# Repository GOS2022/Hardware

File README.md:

# Hardware
This repository contains the design and production files of hardware projects.

# Description
The main goal of hardware projects is to create a compact test device for the OS and service tests.

# Remarks
Contribution to this project is encouraged and appriciated.
If you have any questions or ideas, feel free to contact me: ahmedibrahim.gazar97@gmail.com

Last updated: 2025-07-04
(c) 2025, Ahmed Gazar

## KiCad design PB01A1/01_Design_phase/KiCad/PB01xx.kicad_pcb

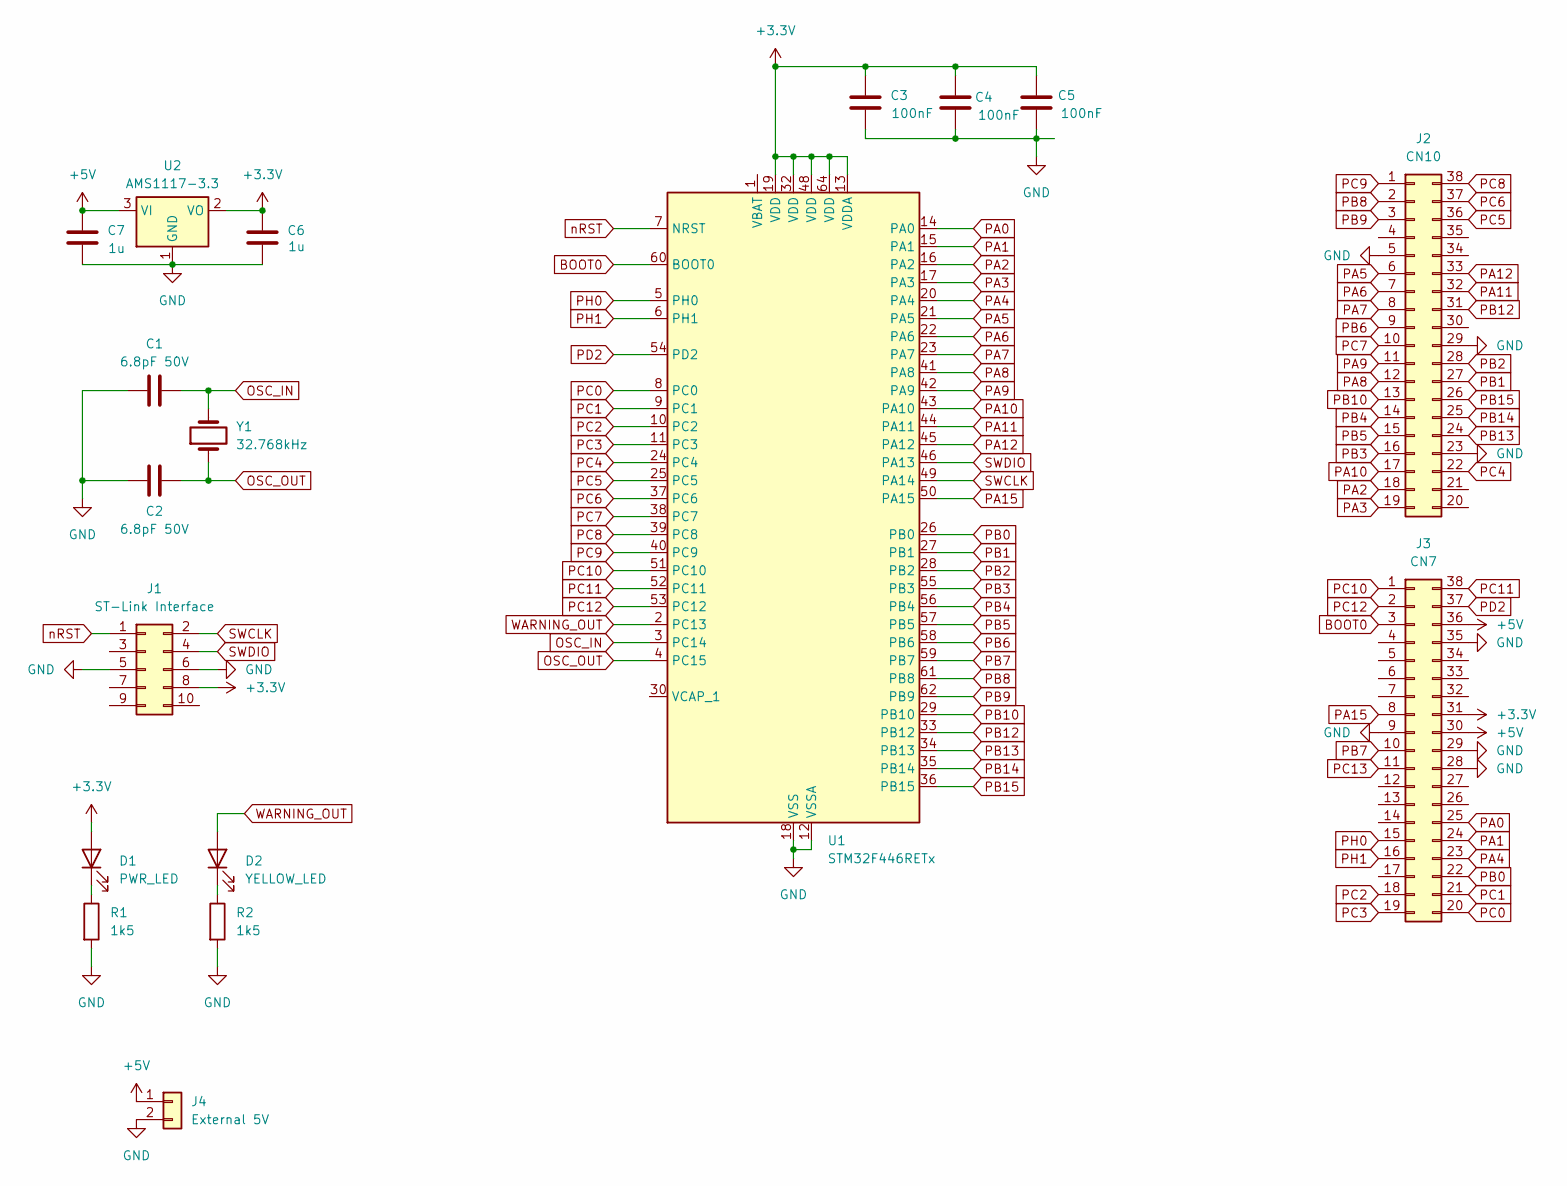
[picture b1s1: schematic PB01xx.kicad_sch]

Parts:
C1, C2: 6.8pF 50V; C_1206_3216Metric_Pad1.33x1.80mm_HandSolder
C3, C4, C5: 100nF; C_1206_3216Metric_Pad1.33x1.80mm_HandSolder
C6, C7: 1u; C_1206_3216Metric_Pad1.33x1.80mm_HandSolder
D1: PWR_LED; LED_1206_3216Metric_Pad1.42x1.75mm_HandSolder
D2: YELLOW_LED; LED_1206_3216Metric_Pad1.42x1.75mm_HandSolder
J1: ST-Link Interface; IDC-Header_2x05_P2.54mm_Vertical
J2: CN10; PinHeader_2x19_P2.54mm_Vertical
J3: CN7; PinHeader_2x19_P2.54mm_Vertical
J4: External 5V; PinHeader_1x02_P2.54mm_Vertical
R1, R2: 1k5; R_1206_3216Metric_Pad1.30x1.75mm_HandSolder
U1: STM32F446RETx; LQFP-64_10x10mm_P0.5mm
U2: AMS1117-3.3; SOT-223-3_TabPin2
Y1: 32.768kHz; Crystal_Round_D3.0mm_Vertical

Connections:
+3.3V: C3.1, C4.1, C5.1, C6.1, D1.2 (A), J1.8, J3.31, U1.13 (VDDA), U1.19 (VDD), U1.32 (VDD), U1.48 (VDD), U1.64 (VDD), U2.2 (VO)
+5V: C7.1, J3.30, J3.36, J4.1, U2.3 (VI)
BOOT0: J3.3, U1.60 (BOOT0)
GND: C1.1, C2.1, C3.2, C4.2, C5.2, C6.2, C7.2, J1.5, J1.6, J2.5, J2.23, J2.29, J3.9, J3.28, J3.29, J3.35, J4.2, R1.2, R2.2, U1.12 (VSSA), U1.18 (VSS), U1.31 (VSS), U1.47 (VSS), U1.63 (VSS), U2.1 (GND)
unnamed: D1.1 (K), R1.1
unnamed: D2.1 (K), R2.1
OSC_IN: C1.2, U1.3 (PC14), Y1.2
OSC_OUT: C2.2, U1.4 (PC15), Y1.1
PA0: J3.25, U1.14 (PA0)
PA1: J3.24, U1.15 (PA1)
PA2: J2.18, U1.16 (PA2)
PA3: J2.19, U1.17 (PA3)
PA4: J3.23, U1.20 (PA4)
PA5: J2.6, U1.21 (PA5)
PA6: J2.7, U1.22 (PA6)
PA7: J2.8, U1.23 (PA7)
PA8: J2.12, U1.41 (PA8)
PA9: J2.11, U1.42 (PA9)
PA10: J2.17, U1.43 (PA10)
PA11: J2.32, U1.44 (PA11)
PA12: J2.33, U1.45 (PA12)
PA15: J3.8, U1.50 (PA15)
PB0: J3.22, U1.26 (PB0)
PB1: J2.27, U1.27 (PB1)
PB2: J2.28, U1.28 (PB2)
PB3: J2.16, U1.55 (PB3)
PB4: J2.14, U1.56 (PB4)
PB5: J2.15, U1.57 (PB5)
PB6: J2.9, U1.58 (PB6)
PB7: J3.10, U1.59 (PB7)
PB8: J2.2, U1.61 (PB8)
PB9: J2.3, U1.62 (PB9)
PB10: J2.13, U1.29 (PB10)
PB12: J2.31, U1.33 (PB12)
PB13: J2.24, U1.34 (PB13)
PB14: J2.25, U1.35 (PB14)
PB15: J2.26, U1.36 (PB15)
PC0: J3.20, U1.8 (PC0)
PC1: J3.21, U1.9 (PC1)
PC2: J3.18, U1.10 (PC2)
PC3: J3.19, U1.11 (PC3)
PC4: J2.22, U1.24 (PC4)
PC5: J2.36, U1.25 (PC5)
PC6: J2.37, U1.37 (PC6)
PC7: J2.10, U1.38 (PC7)
PC8: J2.38, U1.39 (PC8)
PC9: J2.1, U1.40 (PC9)
PC10: J3.1, U1.51 (PC10)
PC11: J3.38, U1.52 (PC11)
PC12: J3.2, U1.53 (PC12)
PC13: J3.11
PD2: J3.37, U1.54 (PD2)
PH0: J3.15, U1.5 (PH0)
PH1: J3.16, U1.6 (PH1)
SWCLK: J1.2, U1.49 (PA14)
SWDIO: J1.4, U1.46 (PA13)
WARNING_OUT: D2.2 (A), U1.2 (PC13)
nRST: J1.1, U1.7 (NRST)

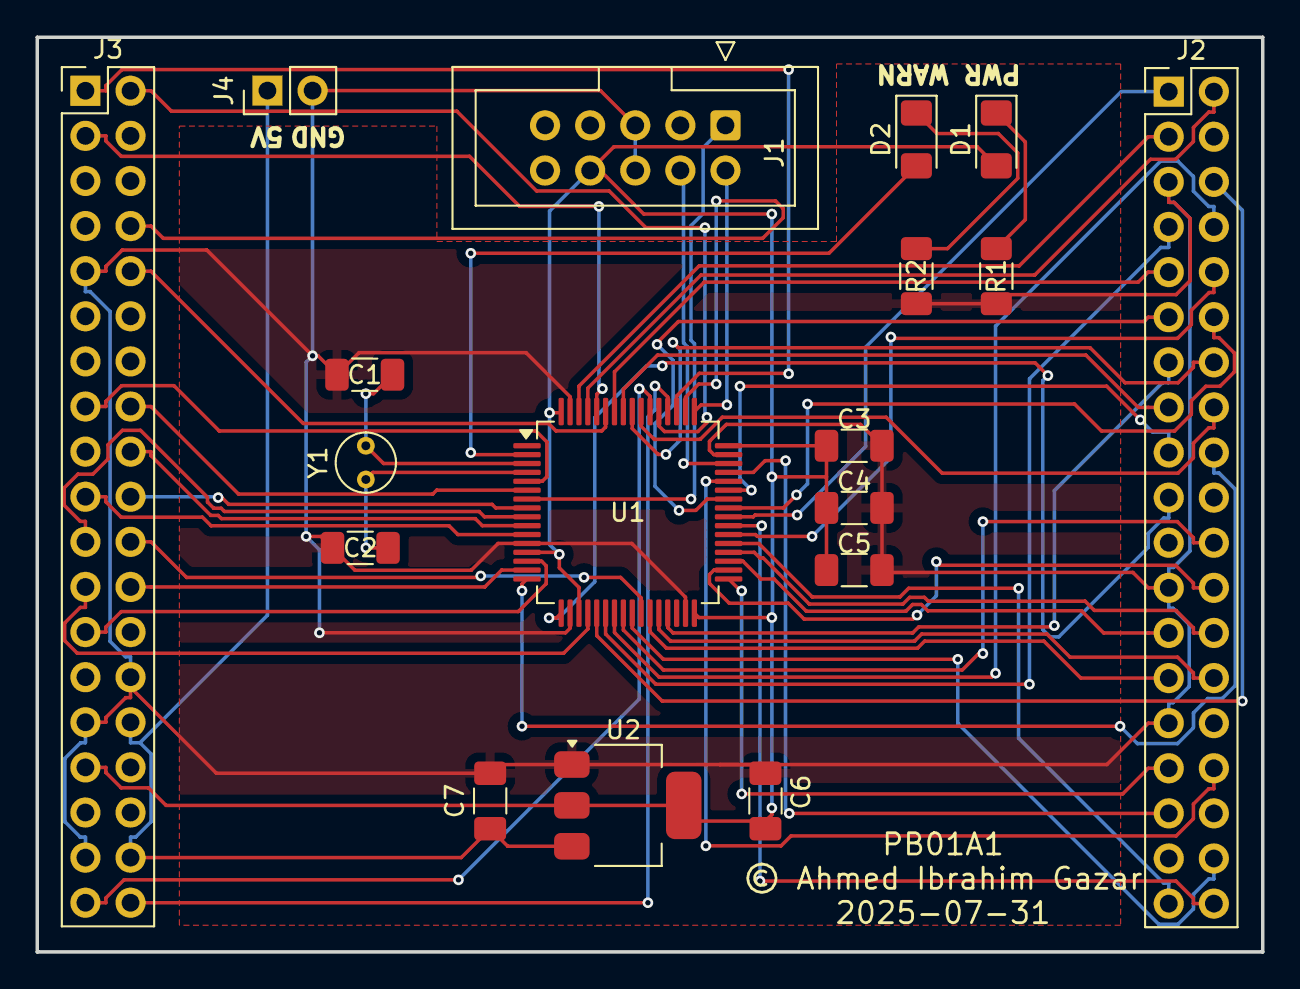
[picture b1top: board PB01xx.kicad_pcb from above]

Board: 2 copper layers, 69.0 x 51.5 mm, 18 parts (0 on the bottom side), 57 nets.

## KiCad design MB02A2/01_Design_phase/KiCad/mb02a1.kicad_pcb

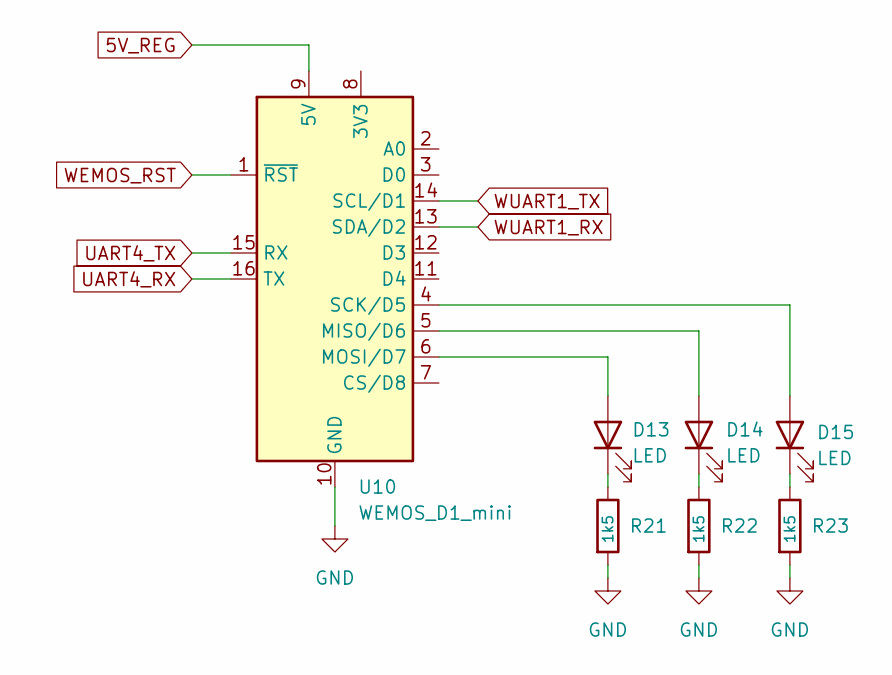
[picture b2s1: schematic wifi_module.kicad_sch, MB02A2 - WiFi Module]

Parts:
D13, D14, D15: LED; LED_1206_3216Metric
R21, R22, R23: 1k5; R_0805_2012Metric
U10: WEMOS_D1_mini; WEMOS_D1_mini_light

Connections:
5V_REG: U10.9 (5V); also elsewhere on the board
GND: R21.2, R22.2, R23.2, U10.10 (GND); also elsewhere on the board
unnamed: D13.2 (A), U10.6 (MOSI/D7)
unnamed: D13.1 (K), R21.1
unnamed: D14.2 (A), U10.5 (MISO/D6)
unnamed: D14.1 (K), R22.1
unnamed: D15.2 (A), U10.4 (SCK/D5)
unnamed: D15.1 (K), R23.1
UART4_RX: U10.16 (TX); also elsewhere on the board
UART4_TX: U10.15 (RX); also elsewhere on the board
WEMOS_RST: U10.1 (~RST); also elsewhere on the board
WUART1_RX: U10.13 (SDA/D2); also elsewhere on the board
WUART1_TX: U10.14 (SCL/D1); also elsewhere on the board

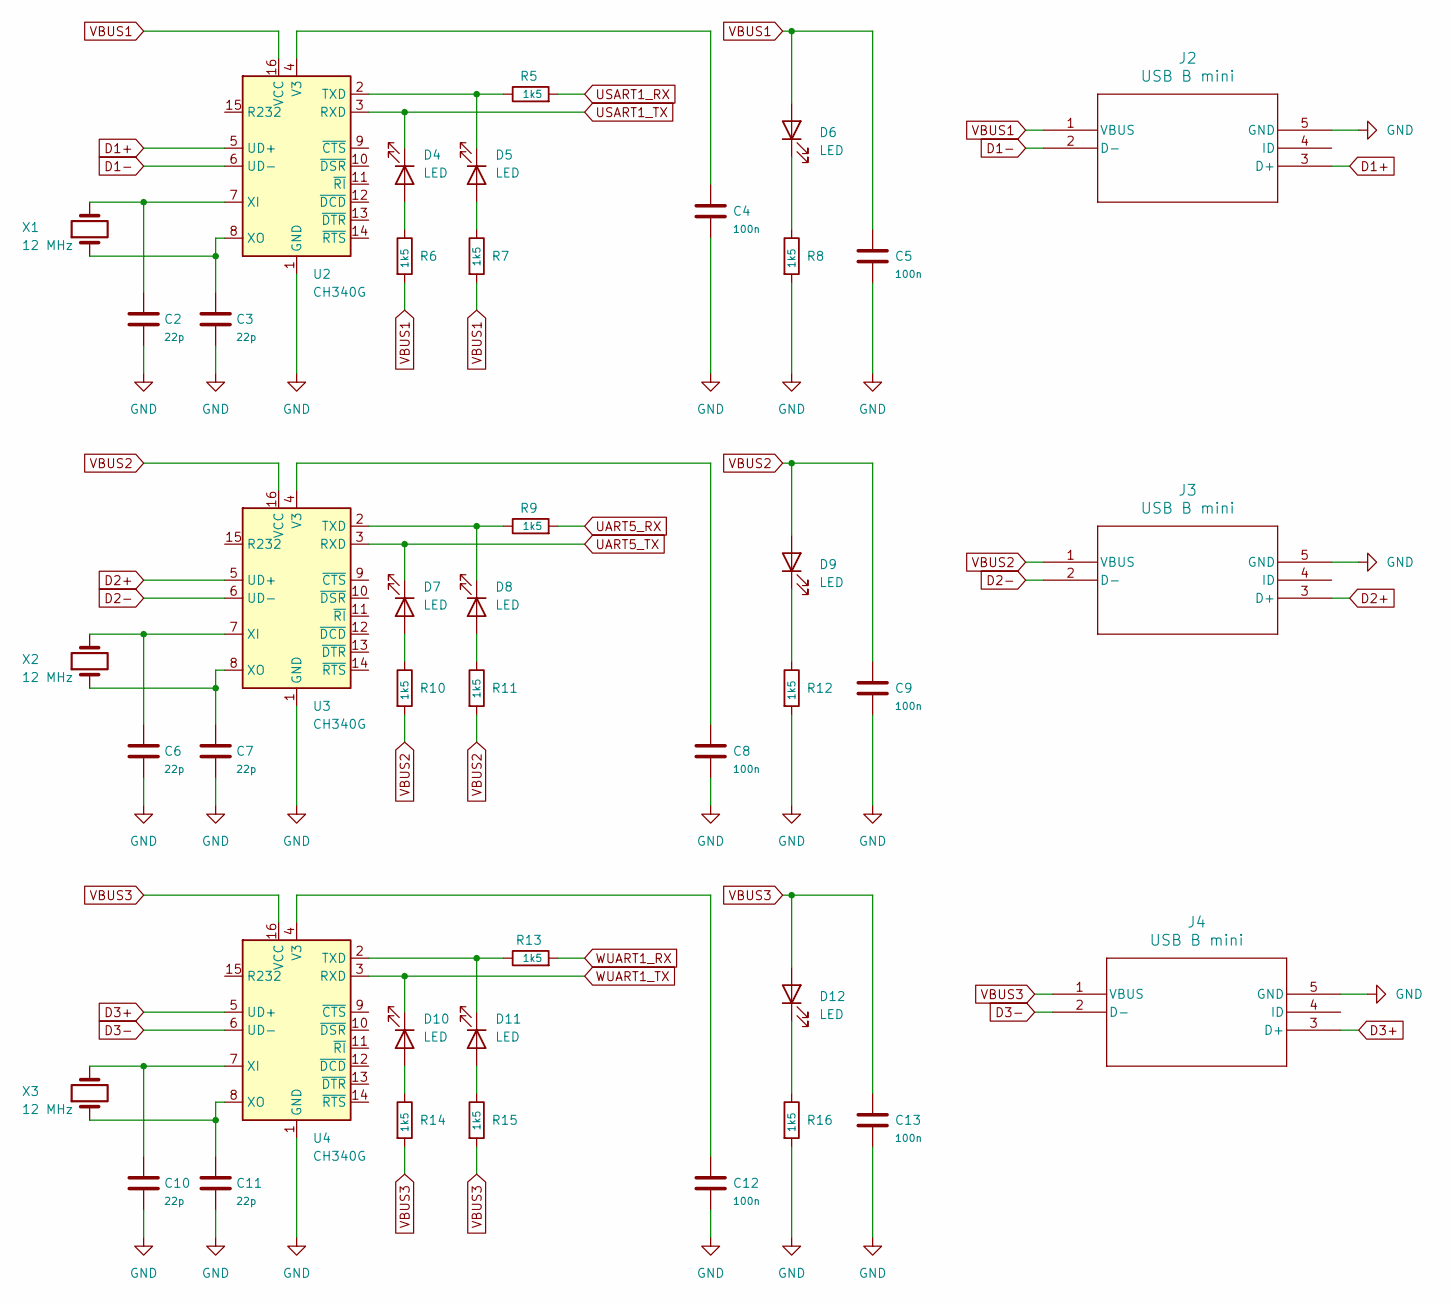
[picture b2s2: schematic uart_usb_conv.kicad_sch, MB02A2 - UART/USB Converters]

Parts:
C2, C3, C6, C7, C10, C11: 22p; C_0805_2012Metric
C4, C5, C8, C9, C12, C13: 100n; C_0805_2012Metric
D4, D5, D6, D7, D8, D9, D10, D11, D12: LED; LED_1206_3216Metric
J2, J3, J4: USB B mini; 54819-0519_MOL
R5, R6, R7, R8, R9, R10, R11, R12, R13, R14, R15, R16: 1k5; R_0805_2012Metric
U2, U3, U4: CH340G; SOIC-16_3.9x9.9mm_P1.27mm
X1, X2, X3: 12 MHz; Crystal_HC49-U_Vertical

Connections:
D1+: J2.3 (D+), U2.5 (UD+)
D1-: J2.2 (D-), U2.6 (UD-)
D2+: J3.3 (D+), U3.5 (UD+)
D2-: J3.2 (D-), U3.6 (UD-)
D3+: J4.3 (D+), U4.5 (UD+)
D3-: J4.2 (D-), U4.6 (UD-)
GND: C2.2, C3.2, C4.2, C5.2, C6.2, C7.2, C8.2, C9.2, C10.2, C11.2, C12.2, C13.2, J2.5 (GND), J3.5 (GND), J4.5 (GND), R8.2, R12.2, R16.2, U2.1 (GND), U3.1 (GND), U4.1 (GND); also elsewhere on the board
unnamed: D4.2 (A), R6.1
unnamed: D5.2 (A), R7.1
unnamed: D5.1 (K), R5.1, U2.2 (TXD)
unnamed: D6.1 (K), R8.1
unnamed: D7.2 (A), R10.1
unnamed: D8.2 (A), R11.1
unnamed: D8.1 (K), R9.1, U3.2 (TXD)
unnamed: D9.1 (K), R12.1
unnamed: D10.2 (A), R14.1
unnamed: D11.2 (A), R15.1
unnamed: D11.1 (K), R13.1, U4.2 (TXD)
unnamed: D12.1 (K), R16.1
unnamed: C4.1, U2.4 (V3)
unnamed: C2.1, U2.7 (XI), X1.2
unnamed: C3.1, U2.8 (XO), X1.1
unnamed: C8.1, U3.4 (V3)
unnamed: C6.1, U3.7 (XI), X2.2
unnamed: C7.1, U3.8 (XO), X2.1
unnamed: C12.1, U4.4 (V3)
unnamed: C10.1, U4.7 (XI), X3.2
unnamed: C11.1, U4.8 (XO), X3.1
UART5_RX: R9.2; also elsewhere on the board
UART5_TX: D7.1 (K), U3.3 (RXD); also elsewhere on the board
USART1_RX: R5.2; also elsewhere on the board
USART1_TX: D4.1 (K), U2.3 (RXD); also elsewhere on the board
VBUS1: C5.1, D6.2 (A), J2.1 (VBUS), R6.2, R7.2, U2.16 (VCC)
VBUS2: C9.1, D9.2 (A), J3.1 (VBUS), R10.2, R11.2, U3.16 (VCC)
VBUS3: C13.1, D12.2 (A), J4.1 (VBUS), R14.2, R15.2, U4.16 (VCC)
WUART1_RX: R13.2; also elsewhere on the board
WUART1_TX: D10.1 (K), U4.3 (RXD); also elsewhere on the board

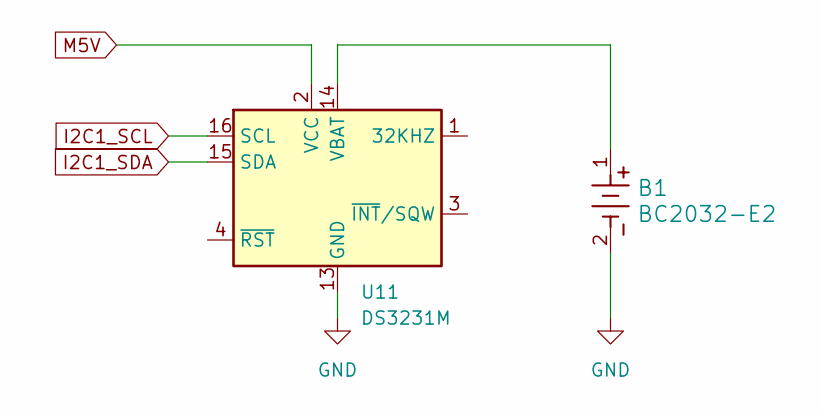
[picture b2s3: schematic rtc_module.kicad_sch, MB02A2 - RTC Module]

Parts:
B1: BC2032-E2; BC2032-E2_MPD
U11: DS3231M; SOIC-16W_7.5x10.3mm_P1.27mm

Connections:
GND: B1.2, U11.5 (GND), U11.6 (GND), U11.7 (GND), U11.8 (GND), U11.9 (GND), U11.10 (GND), U11.11 (GND), U11.12 (GND), U11.13 (GND); also elsewhere on the board
I2C1_SCL: U11.16 (SCL); also elsewhere on the board
I2C1_SDA: U11.15 (SDA); also elsewhere on the board
M5V: U11.2 (VCC); also elsewhere on the board
unnamed: B1.1, U11.14 (VBAT)

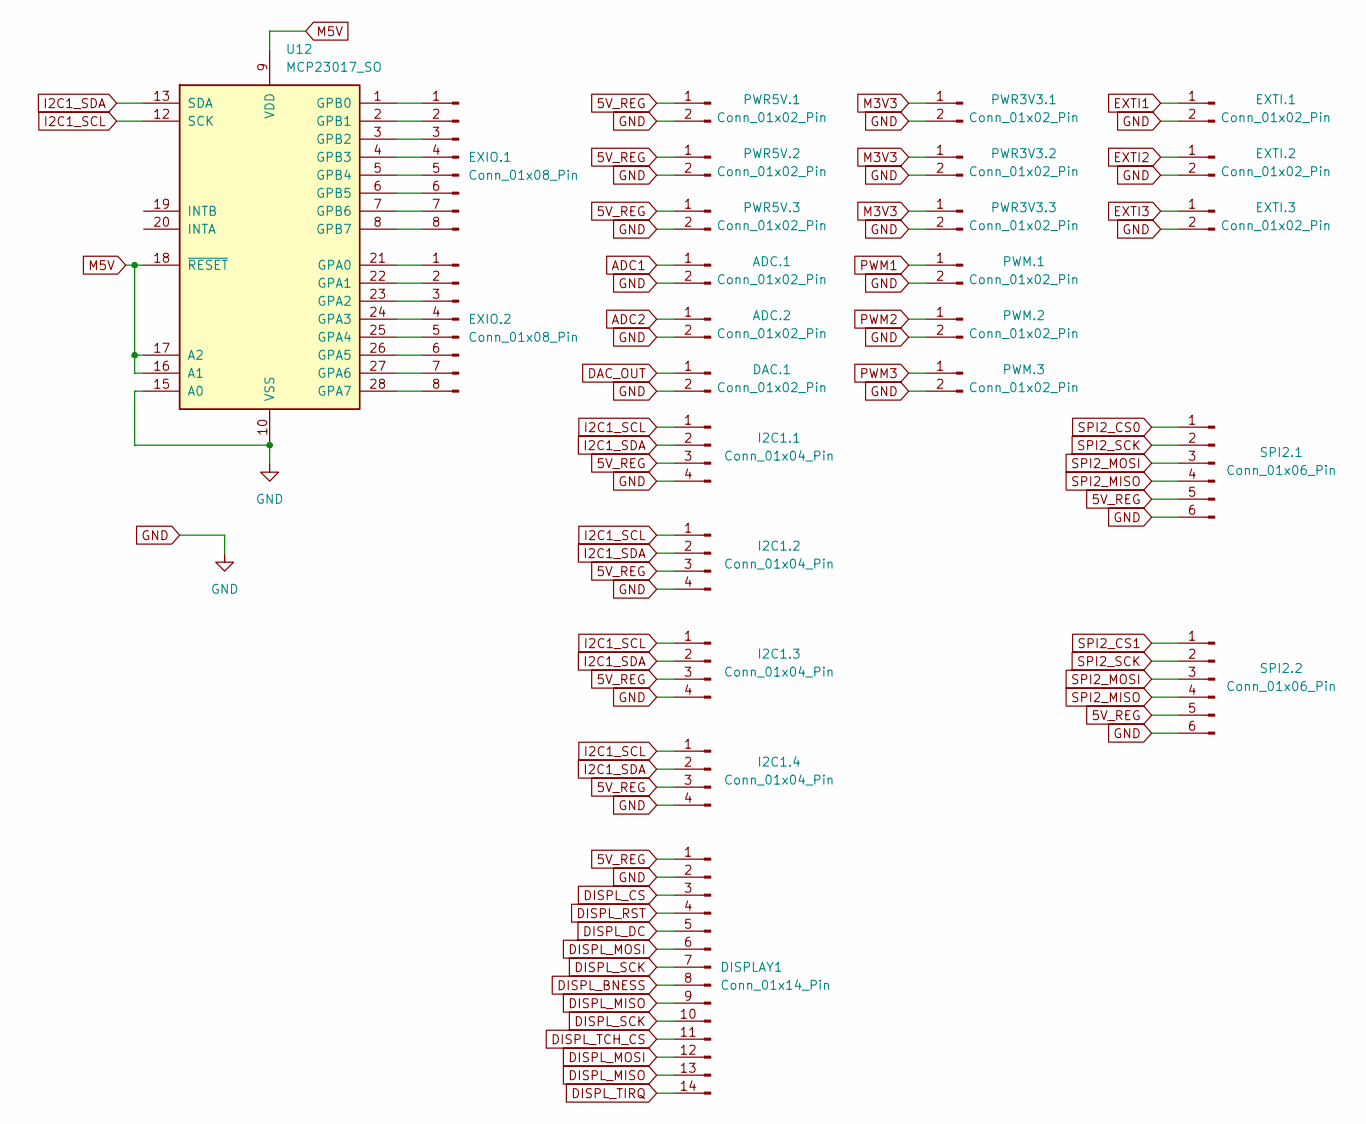
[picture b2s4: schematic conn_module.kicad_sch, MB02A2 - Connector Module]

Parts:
ADC.1, ADC.2: Conn_01x02_Pin; PinHeader_1x02_P2.54mm_Vertical
DAC.1: Conn_01x02_Pin; PinHeader_1x02_P2.54mm_Vertical
DISPLAY1: Conn_01x14_Pin; PinHeader_1x14_P2.54mm_Vertical
EXIO.1, EXIO.2: Conn_01x08_Pin; PinHeader_1x08_P2.54mm_Vertical
EXTI.1, EXTI.2, EXTI.3: Conn_01x02_Pin; PinHeader_1x02_P2.54mm_Vertical
I2C1.1, I2C1.2, I2C1.3, I2C1.4: Conn_01x04_Pin; PinHeader_1x04_P2.54mm_Vertical
PWM.1, PWM.2, PWM.3: Conn_01x02_Pin; PinHeader_1x02_P2.54mm_Vertical
PWR3V3.1, PWR3V3.2, PWR3V3.3, PWR5V.1, PWR5V.2, PWR5V.3: Conn_01x02_Pin; PinHeader_1x02_P2.54mm_Vertical
SPI2.1, SPI2.2: Conn_01x06_Pin; PinHeader_1x06_P2.54mm_Vertical
U12: MCP23017_SO; SOIC-28W_7.5x17.9mm_P1.27mm

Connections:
5V_REG: DISPLAY1.1, I2C1.1.3, I2C1.2.3, I2C1.3.3, I2C1.4.3, PWR5V.1.1, PWR5V.2.1, PWR5V.3.1, SPI2.1.5, SPI2.2.5; also elsewhere on the board
ADC1: ADC.1.1; also elsewhere on the board
ADC2: ADC.2.1; also elsewhere on the board
DAC_OUT: DAC.1.1; also elsewhere on the board
DISPL_BNESS: DISPLAY1.8; also elsewhere on the board
DISPL_CS: DISPLAY1.3; also elsewhere on the board
DISPL_DC: DISPLAY1.5; also elsewhere on the board
DISPL_MISO: DISPLAY1.9, DISPLAY1.13; also elsewhere on the board
DISPL_MOSI: DISPLAY1.6, DISPLAY1.12; also elsewhere on the board
DISPL_RST: DISPLAY1.4; also elsewhere on the board
DISPL_SCK: DISPLAY1.7, DISPLAY1.10; also elsewhere on the board
DISPL_TCH_CS: DISPLAY1.11; also elsewhere on the board
DISPL_TIRQ: DISPLAY1.14; also elsewhere on the board
EXTI1: EXTI.1.1; also elsewhere on the board
EXTI2: EXTI.2.1; also elsewhere on the board
EXTI3: EXTI.3.1; also elsewhere on the board
GND: ADC.1.2, ADC.2.2, DAC.1.2, DISPLAY1.2, EXTI.1.2, EXTI.2.2, EXTI.3.2, I2C1.1.4, I2C1.2.4, I2C1.3.4, I2C1.4.4, PWM.1.2, PWM.2.2, PWM.3.2, PWR3V3.1.2, PWR3V3.2.2, PWR3V3.3.2, PWR5V.1.2, PWR5V.2.2, PWR5V.3.2, SPI2.1.6, SPI2.2.6, U12.10 (VSS), U12.15 (A0); also elsewhere on the board
I2C1_SCL: I2C1.1.1, I2C1.2.1, I2C1.3.1, I2C1.4.1, U12.12 (SCK); also elsewhere on the board
I2C1_SDA: I2C1.1.2, I2C1.2.2, I2C1.3.2, I2C1.4.2, U12.13 (SDA); also elsewhere on the board
M3V3: PWR3V3.1.1, PWR3V3.2.1, PWR3V3.3.1; also elsewhere on the board
M5V: U12.9 (VDD), U12.16 (A1), U12.17 (A2), U12.18 (~RESET); also elsewhere on the board
unnamed: EXIO.1.1, U12.1 (GPB0)
unnamed: EXIO.1.2, U12.2 (GPB1)
unnamed: EXIO.1.3, U12.3 (GPB2)
unnamed: EXIO.1.4, U12.4 (GPB3)
unnamed: EXIO.1.5, U12.5 (GPB4)
unnamed: EXIO.1.6, U12.6 (GPB5)
unnamed: EXIO.1.7, U12.7 (GPB6)
unnamed: EXIO.1.8, U12.8 (GPB7)
unnamed: EXIO.2.1, U12.21 (GPA0)
unnamed: EXIO.2.2, U12.22 (GPA1)
unnamed: EXIO.2.3, U12.23 (GPA2)
unnamed: EXIO.2.4, U12.24 (GPA3)
unnamed: EXIO.2.5, U12.25 (GPA4)
unnamed: EXIO.2.6, U12.26 (GPA5)
unnamed: EXIO.2.7, U12.27 (GPA6)
unnamed: EXIO.2.8, U12.28 (GPA7)
PWM1: PWM.1.1; also elsewhere on the board
PWM2: PWM.2.1; also elsewhere on the board
PWM3: PWM.3.1; also elsewhere on the board
SPI2_CS0: SPI2.1.1; also elsewhere on the board
SPI2_CS1: SPI2.2.1; also elsewhere on the board
SPI2_MISO: SPI2.1.4, SPI2.2.4; also elsewhere on the board
SPI2_MOSI: SPI2.1.3, SPI2.2.3; also elsewhere on the board
SPI2_SCK: SPI2.1.2, SPI2.2.2; also elsewhere on the board

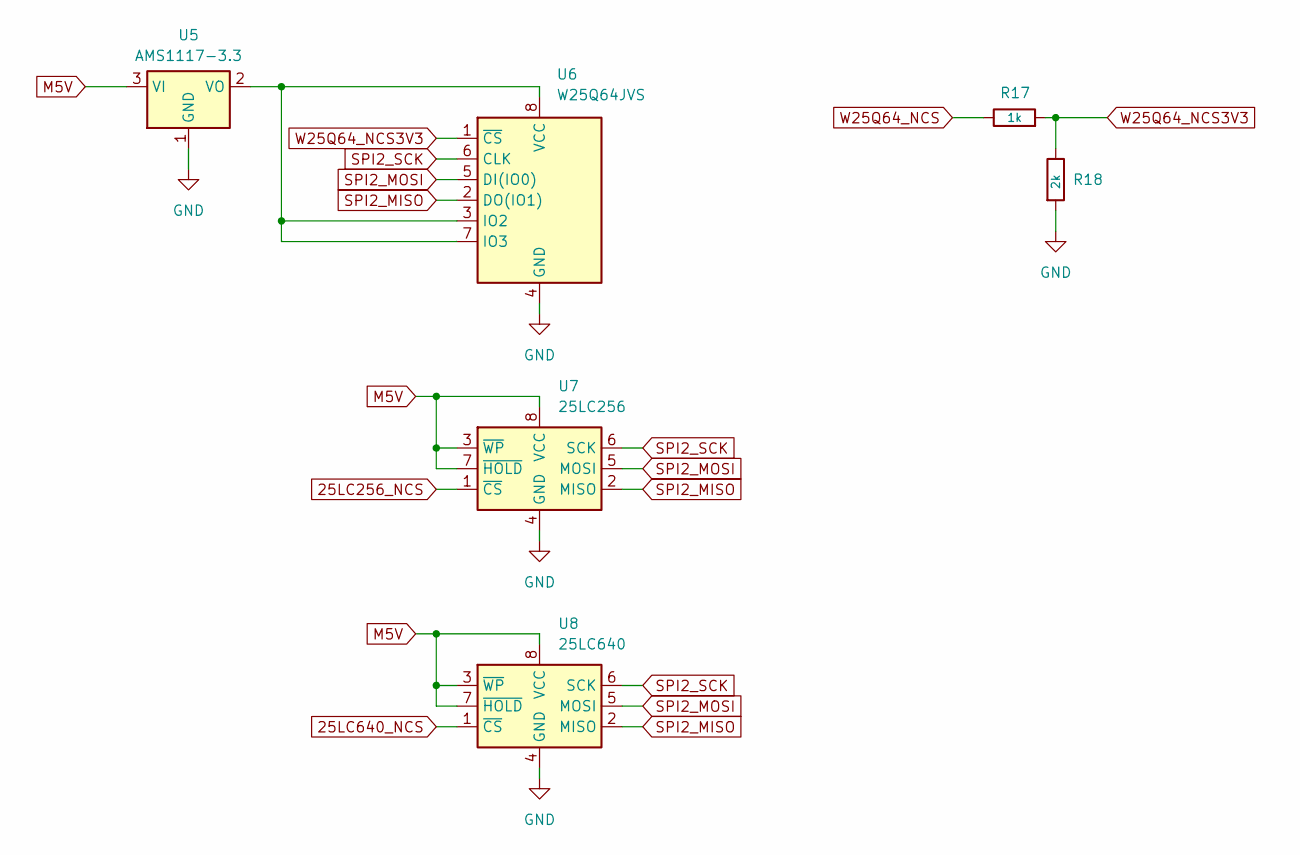
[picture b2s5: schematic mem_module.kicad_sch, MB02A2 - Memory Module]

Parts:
R17: 1k; R_0805_2012Metric
R18: 2k; R_0805_2012Metric
U5: AMS1117-3.3; SOT-223-3_TabPin2
U6: W25Q64JVS; SOIC-8_5.23x5.23mm_P1.27mm
U7: 25LC256; SOIC-8_3.9x4.9mm_P1.27mm
U8: 25LC640; SOIC-8_3.9x4.9mm_P1.27mm

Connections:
25LC256_NCS: U7.1 (~CS); also elsewhere on the board
25LC640_NCS: U8.1 (~CS); also elsewhere on the board
GND: R18.2, U5.1 (GND), U6.4 (GND), U7.4 (GND), U8.4 (GND); also elsewhere on the board
M5V: U5.3 (VI), U7.3 (~WP), U7.7 (~HOLD), U7.8 (VCC), U8.3 (~WP), U8.7 (~HOLD), U8.8 (VCC); also elsewhere on the board
unnamed: U5.2 (VO), U6.3 (IO2), U6.7 (IO3), U6.8 (VCC)
SPI2_MISO: U6.2 (DO(IO1)), U7.2 (MISO), U8.2 (MISO); also elsewhere on the board
SPI2_MOSI: U6.5 (DI(IO0)), U7.5 (MOSI), U8.5 (MOSI); also elsewhere on the board
SPI2_SCK: U6.6 (CLK), U7.6 (SCK), U8.6 (SCK); also elsewhere on the board
W25Q64_NCS: R17.1; also elsewhere on the board
W25Q64_NCS3V3: R17.2, R18.1, U6.1 (~CS)

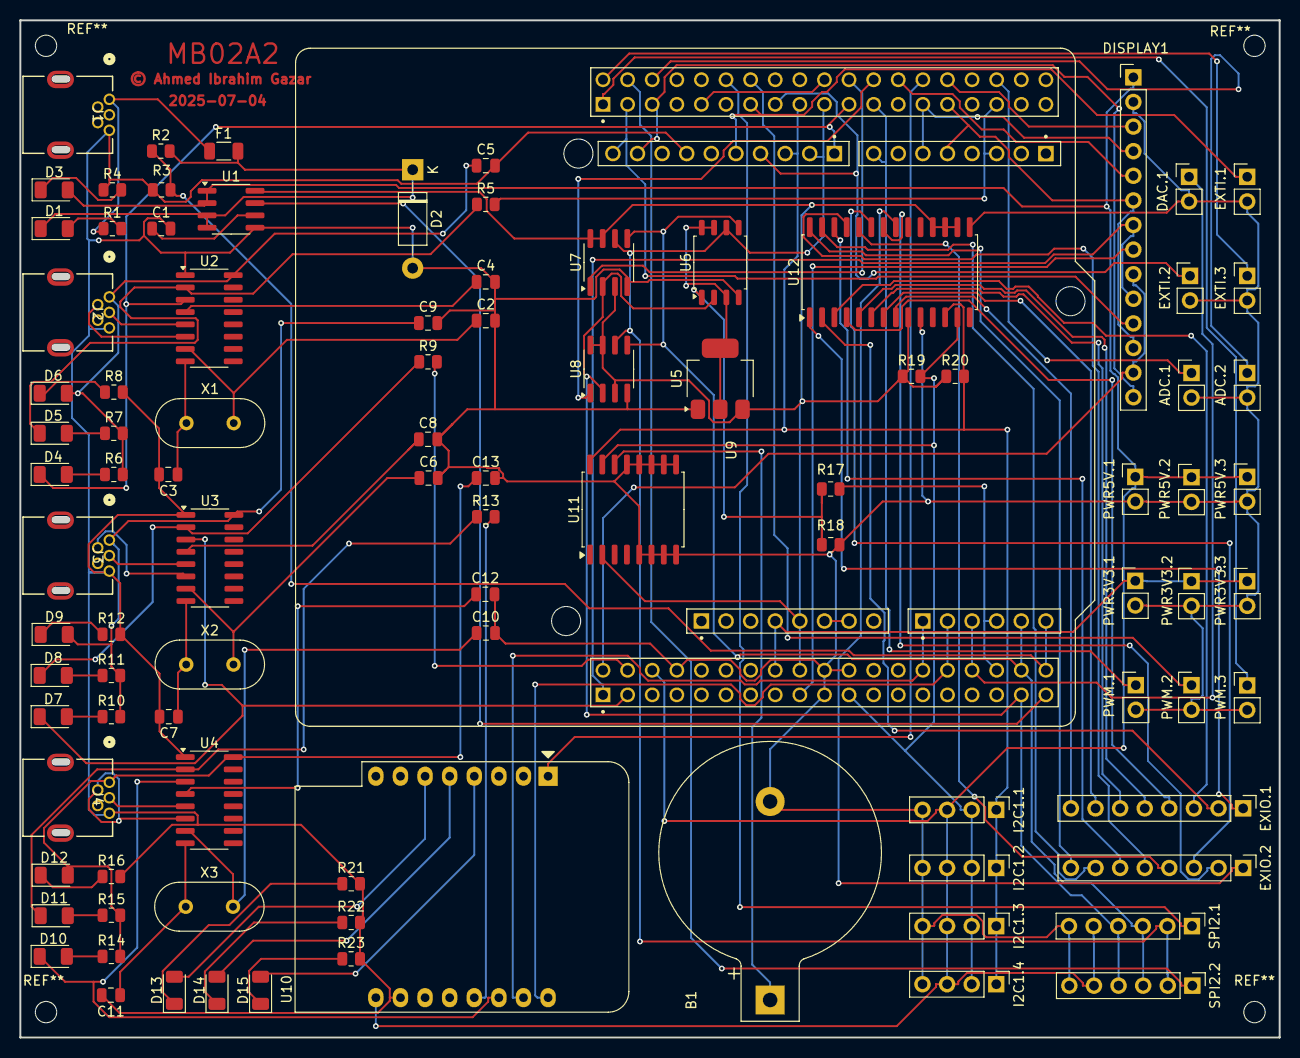
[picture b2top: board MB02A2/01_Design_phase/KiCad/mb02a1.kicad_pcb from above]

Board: 2 copper layers, 130.0 x 105.0 mm, 96 parts (0 on the bottom side), 104 nets.

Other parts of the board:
C1: 1n; C_0805_2012Metric
D1, D3: LED; LED_1206_3216Metric
D2: 1N4001; D_DO-41_SOD81_P10.16mm_Horizontal
F1: RKP-SMDB050; R_1206_3216Metric
J1: USB B mini; 54819-0519_MOL
R1: 220R; R_0805_2012Metric
R2, R3: 10k; R_0805_2012Metric
R4: 1k5; R_0805_2012Metric
R19, R20: 4k7; R_0805_2012Metric
U1: ACS712-05B; SOIC-8_3.9x4.9mm_P1.27mm
U9: NUCLEO-F446RE; MODULE_NUCLEO-F446RE

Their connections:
5V_REG: D3.2 (A), U1.1 (IP+), U1.2 (IP+), U9.CN7_6 (E5V); also elsewhere on the board
25LC256_NCS: U9.CN10_22 (PB2); also elsewhere on the board
25LC640_NCS: U9.CN10_24 (PB1); also elsewhere on the board
ADC1: U9.CN10_34 (PC4); also elsewhere on the board
ADC2: U9.CN10_6 (PC5); also elsewhere on the board
DAC_OUT: U9.CN7_32 (PA4), U9.CN8_3 (A2); also elsewhere on the board
DISPL_BNESS: U9.CN7_17 (PA15); also elsewhere on the board
DISPL_CS: U9.CN10_30 (PB13); also elsewhere on the board
DISPL_DC: U9.CN10_26 (PB15); also elsewhere on the board
DISPL_MISO: U9.CN7_2 (PC11); also elsewhere on the board
DISPL_MOSI: U9.CN9_5 (D4), U9.CN10_29 (PB5); also elsewhere on the board
DISPL_RST: U9.CN9_6 (D5), U9.CN10_27 (PB4); also elsewhere on the board
DISPL_SCK: U9.CN7_1 (PC10); also elsewhere on the board
DISPL_TCH_CS: U9.CN5_10 (D15), U9.CN10_3 (PB8); also elsewhere on the board
DISPL_TIRQ: U9.CN5_9 (D14), U9.CN10_5 (PB9); also elsewhere on the board
EXTI1: U9.CN5_5 (D12), U9.CN10_13 (PA6); also elsewhere on the board
EXTI2: U9.CN5_4 (D11), U9.CN10_15 (PA7); also elsewhere on the board
EXTI3: U9.CN10_2 (PC8); also elsewhere on the board
GND: C1.2, D2.2 (A), J1.5 (GND), R3.1, R4.1, U1.5 (GND), U9.CN5_7 (CN5_GND), U9.CN6_6 (CN6_GND), U9.CN6_7 (CN6_GND), U9.CN7_8 (CN7_GND), U9.CN7_19 (CN7_GND), U9.CN7_20 (CN7_GND), U9.CN7_22 (CN7_GND); also elsewhere on the board
I2C1_SCL: R20.2, U9.CN5_3 (D10), U9.CN10_17 (PB6); also elsewhere on the board
I2C1_SDA: R19.2, U9.CN7_21 (PB7); also elsewhere on the board
I_PWR_MEAS: U1.7 (VIOUT), U9.CN7_37 (PC3)
M3V3: U9.CN6_4 (CN6_+3V3), U9.CN7_16 (CN7_+3V3); also elsewhere on the board
M5V: R19.1, R20.1, U1.8 (VCC), U9.CN6_5 (CN6_+5V), U9.CN7_18 (CN7_+5V); also elsewhere on the board
unnamed: D1.2 (A), R1.2
unnamed: D1.1 (K), D2.1 (K), F1.2, R2.2, U1.3 (IP-), U1.4 (IP-)
unnamed: D3.1 (K), R4.2
unnamed: F1.1, J1.1 (VBUS), R1.1
unnamed: C1.1, U1.6 (FILTER)
unnamed: U9.CN10_9 (CN10_GND), U9.CN10_20 (CN10_GND)
PWM1: U9.CN9_8 (D7), U9.CN10_23 (PA8); also elsewhere on the board
PWM2: U9.CN10_14 (PA11); also elsewhere on the board
PWM3: U9.CN10_1 (PC9); also elsewhere on the board
SPI2_CS0: U9.CN10_12 (PA12); also elsewhere on the board
SPI2_CS1: U9.CN10_4 (PC6); also elsewhere on the board
SPI2_MISO: U9.CN7_35 (PC2); also elsewhere on the board
SPI2_MOSI: U9.CN7_36 (PC1/PB9), U9.CN8_5 (A4); also elsewhere on the board
SPI2_SCK: U9.CN5_2 (D9), U9.CN10_19 (PC7); also elsewhere on the board
UART4_RX: U9.CN7_30 (PA1), U9.CN8_2 (A1); also elsewhere on the board
UART4_TX: U9.CN7_28 (PA0), U9.CN8_1 (A0); also elsewhere on the board
UART5_RX: U9.CN7_4 (PD2); also elsewhere on the board
UART5_TX: U9.CN7_3 (PC12); also elsewhere on the board
USART1_RX: U9.CN9_3 (D2), U9.CN10_33 (PA10); also elsewhere on the board
USART1_TX: U9.CN5_1 (D8), U9.CN10_21 (PA9); also elsewhere on the board
U_PWR_MEAS: R2.1, R3.2, U9.CN7_38 (PC0/PB8), U9.CN8_6 (A5)
W25Q64_NCS: U9.CN7_34 (PB0), U9.CN8_4 (A3); also elsewhere on the board
WEMOS_RST: U9.CN10_28 (PB14); also elsewhere on the board

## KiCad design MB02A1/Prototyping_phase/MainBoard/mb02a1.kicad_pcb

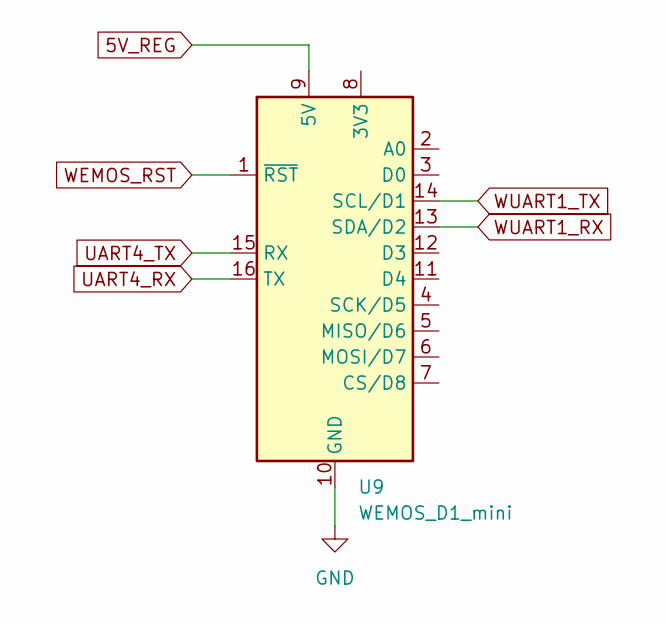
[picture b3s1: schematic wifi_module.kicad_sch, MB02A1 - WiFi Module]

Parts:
U9: WEMOS_D1_mini; WEMOS_D1_mini_light

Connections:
5V_REG: U9.9 (5V); also elsewhere on the board
GND: U9.10 (GND); also elsewhere on the board
UART4_RX: U9.16 (TX); also elsewhere on the board
UART4_TX: U9.15 (RX); also elsewhere on the board
WEMOS_RST: U9.1 (~RST); also elsewhere on the board
WUART1_RX: U9.13 (SDA/D2); also elsewhere on the board
WUART1_TX: U9.14 (SCL/D1); also elsewhere on the board

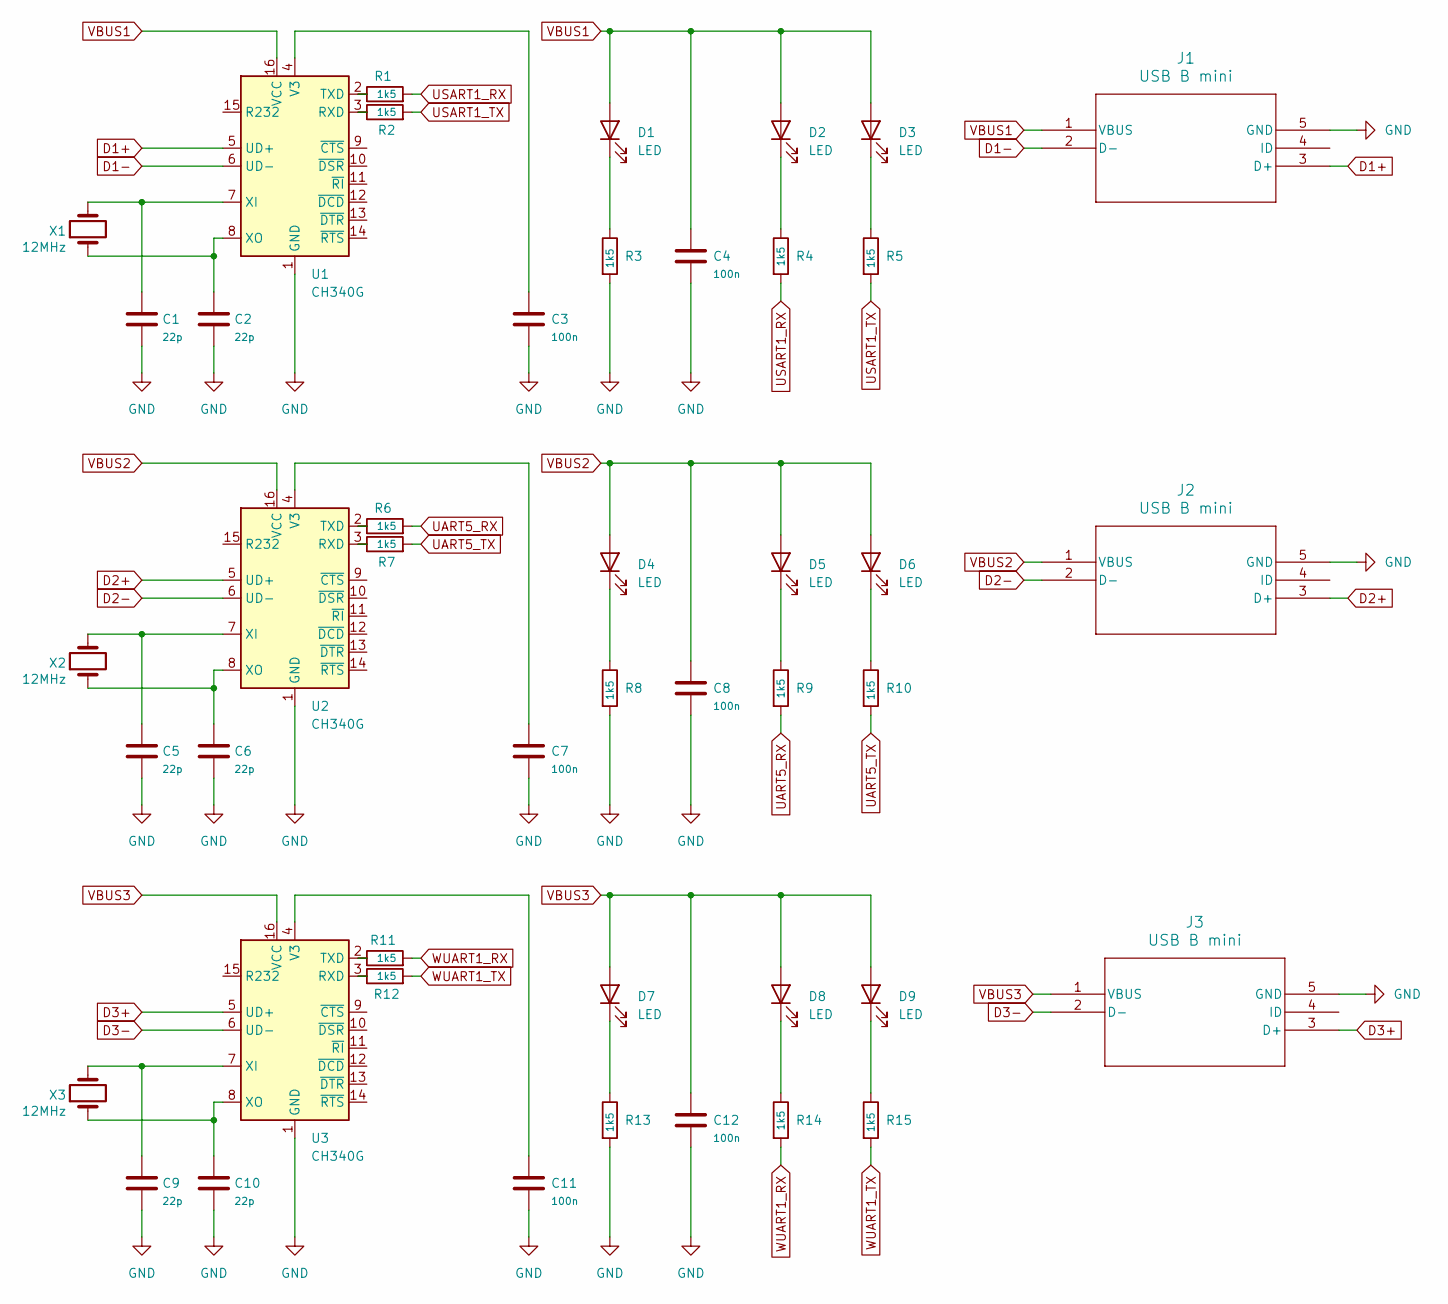
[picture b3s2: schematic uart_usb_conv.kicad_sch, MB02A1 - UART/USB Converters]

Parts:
C1, C2, C5, C6, C9, C10: 22p; C_0805_2012Metric
C3, C4, C7, C8, C11, C12: 100n; C_0805_2012Metric
D1, D2, D3, D4, D5, D6, D7, D8, D9: LED; LED_1206_3216Metric
J1, J2, J3: USB B mini; 54819-0519_MOL
R1, R2, R3, R4, R5, R6, R7, R8, R9, R10, R11, R12, R13, R14, R15: 1k5; R_0805_2012Metric
U1, U2, U3: CH340G; SOIC-16_3.9x9.9mm_P1.27mm
X1, X2, X3: 12MHz; Crystal_HC18-U_Vertical

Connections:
D1+: J1.3 (D+), U1.5 (UD+)
D1-: J1.2 (D-), U1.6 (UD-)
D2+: J2.3 (D+), U2.5 (UD+)
D2-: J2.2 (D-), U2.6 (UD-)
D3+: J3.3 (D+), U3.5 (UD+)
D3-: J3.2 (D-), U3.6 (UD-)
GND: C1.2, C2.2, C3.2, C4.2, C5.2, C6.2, C7.2, C8.2, C9.2, C10.2, C11.2, C12.2, J1.5 (GND), J2.5 (GND), J3.5 (GND), R3.2, R8.2, R13.2, U1.1 (GND), U2.1 (GND), U3.1 (GND); also elsewhere on the board
unnamed: D1.1 (K), R3.1
unnamed: D2.1 (K), R4.1
unnamed: D3.1 (K), R5.1
unnamed: D4.1 (K), R8.1
unnamed: D5.1 (K), R9.1
unnamed: D6.1 (K), R10.1
unnamed: D7.1 (K), R13.1
unnamed: D8.1 (K), R14.1
unnamed: D9.1 (K), R15.1
unnamed: R2.1, U1.3 (RXD)
unnamed: R1.1, U1.2 (TXD)
unnamed: C3.1, U1.4 (V3)
unnamed: C1.1, U1.7 (XI), X1.2
unnamed: C2.1, U1.8 (XO), X1.1
unnamed: R7.1, U2.3 (RXD)
unnamed: R6.1, U2.2 (TXD)
unnamed: C7.1, U2.4 (V3)
unnamed: C5.1, U2.7 (XI), X2.2
unnamed: C6.1, U2.8 (XO), X2.1
unnamed: R12.1, U3.3 (RXD)
unnamed: R11.1, U3.2 (TXD)
unnamed: C11.1, U3.4 (V3)
unnamed: C9.1, U3.7 (XI), X3.2
unnamed: C10.1, U3.8 (XO), X3.1
UART5_RX: R6.2, R9.2; also elsewhere on the board
UART5_TX: R7.2, R10.2; also elsewhere on the board
USART1_RX: R1.2, R4.2; also elsewhere on the board
USART1_TX: R2.2, R5.2; also elsewhere on the board
VBUS1: C4.1, D1.2 (A), D2.2 (A), D3.2 (A), J1.1 (VBUS), U1.16 (VCC)
VBUS2: C8.1, D4.2 (A), D5.2 (A), D6.2 (A), J2.1 (VBUS), U2.16 (VCC)
VBUS3: C12.1, D7.2 (A), D8.2 (A), D9.2 (A), J3.1 (VBUS), U3.16 (VCC)
WUART1_RX: R11.2, R14.2; also elsewhere on the board
WUART1_TX: R12.2, R15.2; also elsewhere on the board

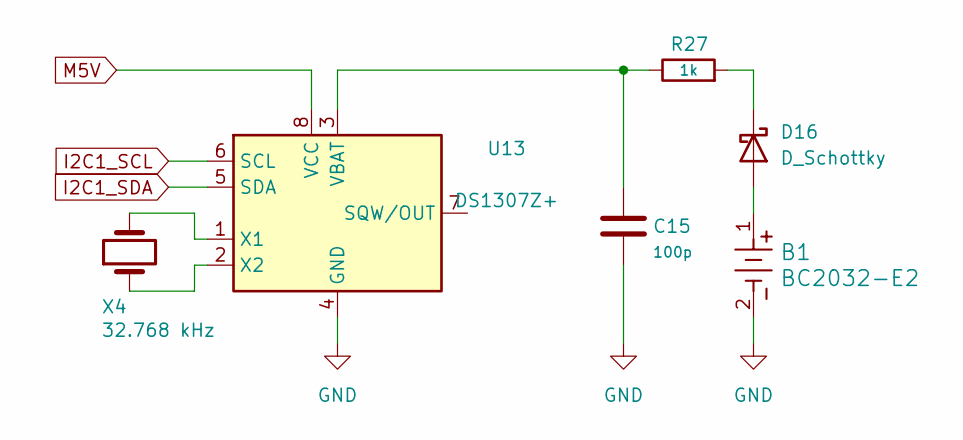
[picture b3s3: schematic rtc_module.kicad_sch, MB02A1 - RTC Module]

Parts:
B1: BC2032-E2; BC2032-E2_MPD
C15: 100p; C_0805_2012Metric
D16: D_Schottky; D_1206_3216Metric
R27: 1k; R_0805_2012Metric
U13: DS1307Z+; SOIC-8_3.9x4.9mm_P1.27mm
X4: 32.768 kHz; Crystal_HC18-U_Vertical

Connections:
GND: B1.2, C15.2, U13.4 (GND); also elsewhere on the board
I2C1_SCL: U13.6 (SCL); also elsewhere on the board
I2C1_SDA: U13.5 (SDA); also elsewhere on the board
M5V: U13.8 (VCC); also elsewhere on the board
unnamed: B1.1, D16.2 (A)
unnamed: D16.1 (K), R27.2
unnamed: C15.1, R27.1, U13.3 (VBAT)
unnamed: U13.1 (X1), X4.2
unnamed: U13.2 (X2), X4.1

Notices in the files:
MB02A2/01_Design_phase/KiCad/mb02a1.kicad_pcb:
© Ahmed Ibrahim Gazar
